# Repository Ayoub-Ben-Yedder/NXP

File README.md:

# NXP Line Following Robot

An autonomous 2line-following robot built on the Teensy microcontroller with advanced vision-based steering using Pixy2 camera. Designed for precision line tracking with intersection detection and obstacle avoidance.

## Project Overview

This project implements a sophisticated autonomous robot controller that:
- Follows lines detected by Pixy2 camera vision system
- Intelligently handles intersections and corners
- Detects and responds to obstacles using ultrasonic distance sensor
- Recognizes finish line patterns and stops safely
- Applies advanced steering algorithms for smooth, stable tracking

## Hardware Components

### Microcontroller
- **Teensy** (primary controller)

### Sensors
- **Pixy2 Camera** - Line detection and vector tracking
- **HC-SR04 Ultrasonic Sensor** - Distance measurement for obstacle detection
  - TRIG: Pin 14
  - ECHO: Pin 15

### Actuators
- **Servo Motor** - Steering control (Pin 23)
- **DC Motors (x2)** - Left and right propulsion
  - Left Motor: PWM (Pin 8), Direction (Pins 6-7)
  - Right Motor: PWM (Pin 18), Direction (Pins 20-19)

### Additional
- **LED Indicator** - Pin 22
- **Logic Level Converters** - For Pixy2 communication

## Electronics & PCB Design

The electronics are primarily a **Teensy 4.0 shield** custom designed with **KiCAD**. The shield integrates all necessary components (motor drivers, sensor interfaces, power distribution) onto a single PCB that stacks directly onto the Teensy 4.0 microcontroller, providing a clean and compact solution for the robot.

### Schematics

### PCB Layout

### 3D View

All design files are located in the `electronics/` directory.

## Mechanical Design

The mechanical design for this robot was adapted from the [NXP CUP FINALS](https://github.com/aminebensaid66/NXP-CUP-FINALS) repository. This includes the chassis, motor mounts, sensor brackets, and other structural components required for the robot assembly.

## Pin Configuration

```
PWM1 = 8      (Left motor speed)
IN1 = 6       (Left motor direction)
IN2 = 7       (Left motor direction)
PWM2 = 18     (Right motor speed)
IN3 = 20      (Right motor direction)
IN4 = 19      (Right motor direction)

LED = 22
ECHO = 15     (Ultrasonic echo)
TRIG = 14     (Ultrasonic trigger)
SERVO_PIN = 23 (Steering servo)
```

## Key Features

### 1. Advanced Line Following
- Processes up to 20 line vectors from Pixy2 camera
- Weighted steering algorithm that considers vector angles and lengths
- Minimum vector length filtering to ignore noise
- Soft steering limits to prevent oscillation

### 2. Intersection Detection
- Identifies corner types: top-left, top-right, bottom-left, bottom-right
- Analyzes angle between consecutive vectors (target ~90°)
- Applies directional corrections based on intersection position
- More aggressive steering during turns for accuracy

### 3. Steering Control
- **Center Angle:** 135° (neutral position)
- **Steering Range:** 90° (MAX_LEFT) to 180° (MAX_RIGHT)
- **Deadband:** ±15° around forward angle to filter horizontal noise
- **Soft Limiting:** Reduces extreme steering angles to prevent oscillation
- **Center Bias:** Gently pulls steering toward center for stability
- **Delay System:** Smooths steering inputs over 2 cycles

### 4. Obstacle Detection & Avoidance
- Continuously monitors distance via ultrasonic sensor
- Filtered readings (average of 3 samples) for stability
- **Stop Distance:** 15 cm - triggers reverse and stop
- Timeout handling for cases where no object is detected

### 5. Finish Line Recognition
- Detects horizontal line patterns (angle ≤ 15° from horizontal)
- Requires 2+ horizontal vectors within 5 pixels of each other
- Activation delay (10 seconds) to avoid false positives at start
- Triggers acceleration boost and obstacle check

## Build & Upload

This project uses **PlatformIO** for build and upload management.

### Prerequisites
- VSCode with PlatformIO extension
- Arduino IDE libraries (Pixy2, Servo)

### Building
```bash
pio run
```

### Uploading to Device
```bash
pio run --target upload
```

### Monitoring Serial Output
```bash
pio device monitor
```

## Algorithm Flow

1. **Initialization**
   - Configure PWM frequencies (20 kHz)
   - Initialize pins and servo to center
   - Initialize Pixy2 in line-tracking mode
   - Record start time for finish line delay

2. **Main Loop (runNXP)**
   - Read Pixy2 vectors
   - Filter vectors by length, angle, and position
   - Identify horizontal vectors for finish line detection
   - Sort vectors by length (longest first)
   - Compute steering angle based on vector count:
     - **0 vectors:** Maintain last angle
     - **1 vector:** Standard line following
     - **2+ vectors:** Check for intersection; if ~90° angle detected, apply intersection steering
   - Apply steering corrections (center bias, soft limits)
   - Implement steering delay system for smooth transitions
   - Check finish line and obstacle avoidance conditions

3. **Distance Monitoring**
   - Triggered after finish line detection
   - Backs up and stops if obstacle within STOP_DISTANCE

## Constants & Tuning Parameters

```cpp
MAX_VECTORS = 20          // Max vectors to process per frame
MIN_VECTOR_LENGTH = 10    // Minimum pixels for valid vector

CENTRE_ANGLE = 135        // Neutral steering position
MAX_RIGHT = 180           // Maximum right turn
MAX_LEFT = 90             // Maximum left turn

STOP_DISTANCE = 15        // cm - obstacle stop threshold

PIXY_FORWARD_ANGLE = 270  // Expected angle for straight tracking
PIXY_STEER_DEADBAND = 15  // Angle tolerance for horizontal detection
STEERING_DELAY_CYCLES = 2 // Smoothing delay for steering changes
STEERING_QUEUE_THRESHOLD = 2.0   // Threshold to queue steering change
STEERING_CENTER_BIAS = 5.0       // Pull toward center amount
STEERING_SOFT_LIMIT_START = 11   // When to start softening
STEERING_SOFT_LIMIT_FACTOR = 0.5 // Softening strength
CROSS_CORRECTION_ANGLE = 15      // Intersection correction
```

## Performance Notes

- **Steering Response:** Balanced between responsiveness and stability
- **Motor Speed:** Default 150 units for forward motion, 130 for finish line
- **Reverse Speed:** 100 units for obstacle avoidance
- **Frame Rate:** Dependent on Pixy2 refresh rate (typical ~50 FPS)

## Troubleshooting

| Issue | Solution |
|-------|----------|
| Robot doesn't follow line | Check Pixy2 is in "line" mode; verify camera focus; check lighting |
| Erratic steering | Increase STEERING_DELAY_CYCLES; adjust STEERING_CENTER_BIAS |
| Misses turns | Lower angle threshold in intersection detection; increase CROSS_CORRECTION_ANGLE |
| Oscillates | Enable soft limiting; increase STEERING_SOFT_LIMIT_FACTOR |
| Overshoots finish line | Reduce finish line acceleration value; increase STOP_DISTANCE |

## Project Structure

```
NXP/
├── src/
│   ├── main.cpp          # Main robot controller
│   └── README.md         # This file
├── include/
├── lib/
├── platformio.ini        # Build configuration
└── test/
```

## Future Enhancements

- PID control for smoother steering response
- Dynamic speed adjustment based on turn sharpness
- Gyro integration for improved angle estimation
- Adaptive threshold tuning based on lighting conditions
- Multi-point finish line detection for reliability

---

**Last Updated:** June 2026  
**Board:** Teensy  
**Camera:** Pixy2  
**Competition:** NXP

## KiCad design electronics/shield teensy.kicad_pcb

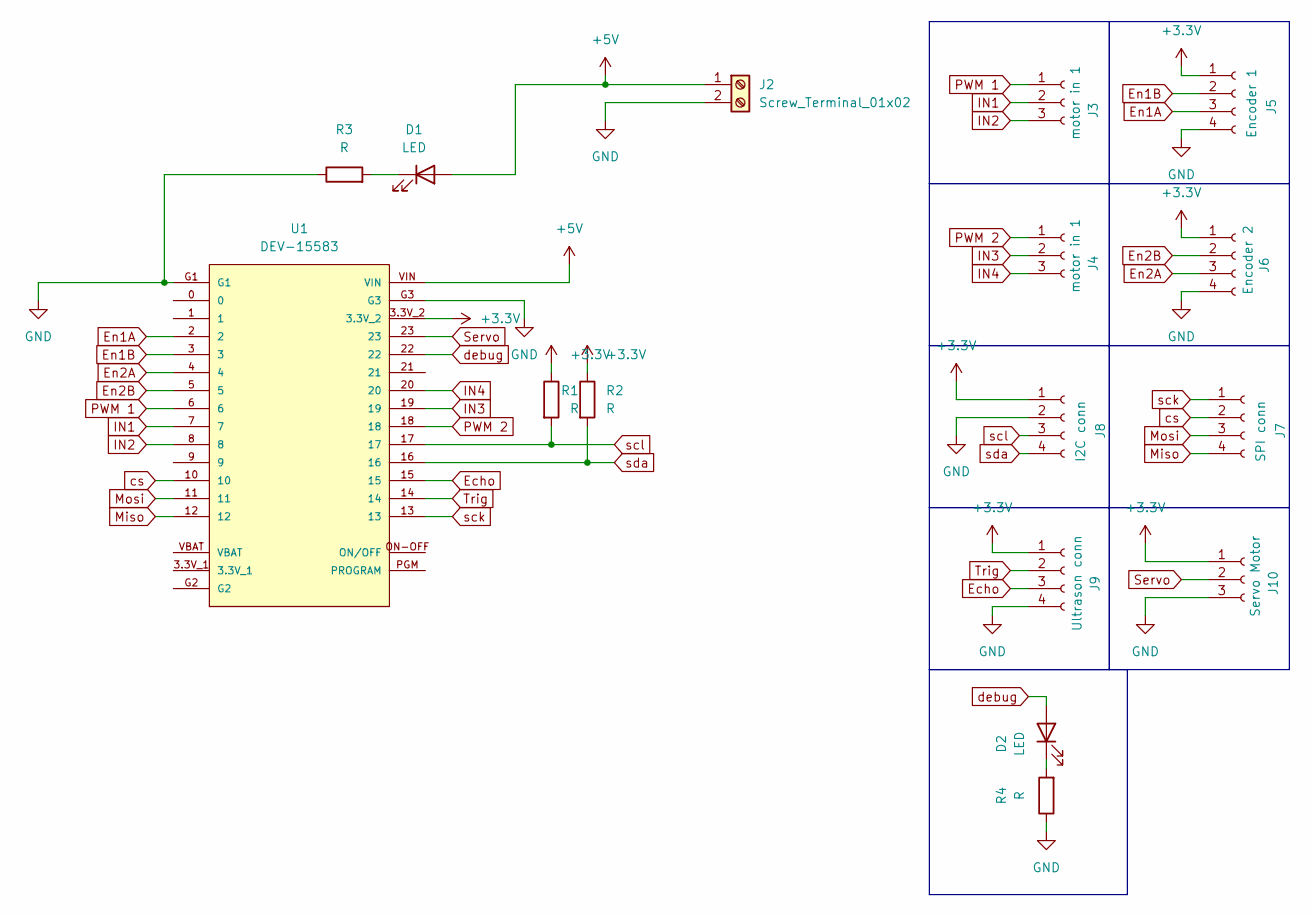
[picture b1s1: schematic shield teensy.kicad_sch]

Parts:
D1, D2: LED; LED_D3.0mm
J2: Screw_Terminal_01x02; TerminalBlock_MetzConnect_Type055_RT01502HDWU_1x02_P5.00mm_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
J3, J4: motor in 1; JST_XH_B3B-XH-A_1x03_P2.50mm_Vertical
J5: Encoder 1; JST_XH_B4B-XH-A_1x04_P2.50mm_Vertical
J6: Encoder 2; JST_XH_B4B-XH-A_1x04_P2.50mm_Vertical
J7: SPI conn; JST_XH_B4B-XH-A_1x04_P2.50mm_Vertical
J8: I2C conn; JST_XH_B4B-XH-A_1x04_P2.50mm_Vertical
J9: Ultrason conn; JST_XH_B4B-XH-A_1x04_P2.50mm_Vertical
J10: Servo Motor; JST_XH_B3B-XH-A_1x03_P2.50mm_Vertical
R1, R2: R; R_Axial_DIN0207_L6.3mm_D2.5mm_P7.62mm_Horizontal
R3, R4: R; R_Axial_DIN0207_L6.3mm_D2.5mm_P2.54mm_Vertical
U1: DEV-15583; MODULE_DEV-15583

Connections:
+3.3V: J5.1, J6.1, J8.1, J9.1, J10.1, R1.1, R2.1, U1.3.3V_2
+5V: D1.2 (A), J2.1, U1.VIN
Echo: J9.3, U1.15
En1A: J5.3, U1.2
En1B: J5.2, U1.3
En2A: J6.3, U1.4
En2B: J6.2, U1.5
GND: J2.2, J5.4, J6.4, J8.2, J9.4, J10.3, R3.1, R4.1, U1.G1, U1.G3
IN1: J3.2, U1.7
IN2: J3.3, U1.8
IN3: J4.2, U1.19
IN4: J4.3, U1.20
Miso: J7.4, U1.12
Mosi: J7.3, U1.11
unnamed: D1.1 (K), R3.2
unnamed: D2.1 (K), R4.2
PWM 1: J3.1, U1.6
PWM 2: J4.1, U1.18
Servo: J10.2, U1.23
Trig: J9.2, U1.14
cs: J7.2, U1.10
debug: D2.2 (A), U1.22
sck: J7.1, U1.13
scl: J8.3, R1.2, U1.17
sda: J8.4, R2.2, U1.16

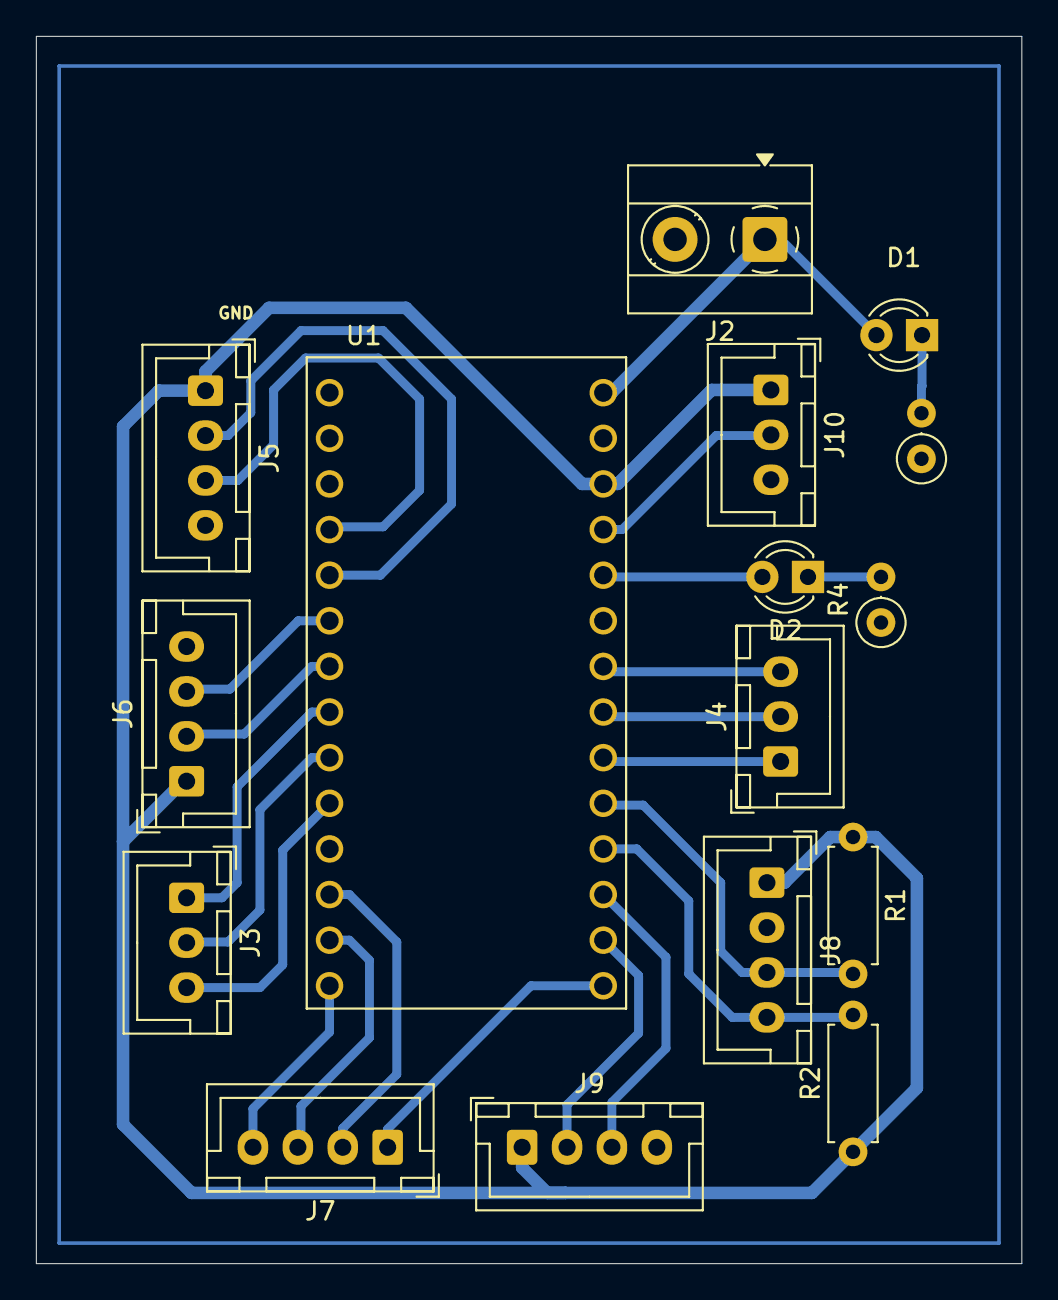
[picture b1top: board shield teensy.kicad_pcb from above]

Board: 2 copper layers, 54.9 x 68.3 mm, 16 parts (0 on the bottom side), 25 nets.

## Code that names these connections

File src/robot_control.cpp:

#include <Arduino.h>
#include <Pixy2.h>
#include <Servo.h>

#include "robot_control.h"

namespace {

constexpr uint8_t ENC_LEFT_A = 4;
constexpr uint8_t ENC_LEFT_B = 5;
constexpr uint8_t ENC_RIGHT_A = 3;
constexpr uint8_t ENC_RIGHT_B = 2;

constexpr uint8_t PWM1 = 8;
constexpr uint8_t IN1 = 6;
constexpr uint8_t IN2 = 7;
constexpr uint8_t PWM2 = 18;
constexpr uint8_t IN3 = 20;
constexpr uint8_t IN4 = 19;

constexpr uint8_t LED = 22;

constexpr uint8_t ECHO = 15;
constexpr uint8_t TRIG = 14;

constexpr uint8_t SERVO_PIN = 23;

Servo steer_servo;
Pixy2 pixy;

void leftEncoderISR() {
  if (digitalReadFast(ENC_LEFT_B) == digitalReadFast(ENC_LEFT_A)) {
    leftCount++;
  } else {
    leftCount--;
  }
}

void rightEncoderISR() {
  if (digitalReadFast(ENC_RIGHT_B) == digitalReadFast(ENC_RIGHT_A)) {
    rightCount++;
  } else {
    rightCount--;
  }
}

}  // namespace

volatile long leftCount = 0;
volatile long rightCount = 0;

void initPixy() {
  pixy.init();
  pixy.changeProg("line");
}

void steer(int angle) {
  angle = constrain(angle, MAX_LEFT, MAX_RIGHT);
  steer_servo.write(angle);
}

void run(int speedLeft, int speedRight) {
  speedLeft = constrain(speedLeft, -255, 255);
  speedRight = constrain(speedRight, -255, 255);

  if (speedRight >= 0) {
    analogWrite(PWM2, speedRight);
    digitalWrite(IN3, HIGH);
    digitalWrite(IN4, LOW);
  } else {
    analogWrite(PWM2, -speedRight);
    digitalWrite(IN3, LOW);
    digitalWrite(IN4, HIGH);
  }

  if (speedLeft >= 0) {
    analogWrite(PWM1, speedLeft);
    digitalWrite(IN1, LOW);
    digitalWrite(IN2, HIGH);
  } else {
    analogWrite(PWM1, -speedLeft);
    digitalWrite(IN1, HIGH);
    digitalWrite(IN2, LOW);
  }
}

void robot_control_setup() {
  analogWriteResolution(8);
  analogWriteFrequency(PWM1, 20000);
  analogWriteFrequency(PWM2, 20000);

  pinMode(TRIG, OUTPUT);
  pinMode(ECHO, INPUT);
  pinMode(LED, OUTPUT);

  pinMode(PWM1, OUTPUT);
  pinMode(PWM2, OUTPUT);

  pinMode(IN1, OUTPUT);
  pinMode(IN2, OUTPUT);
  pinMode(IN3, OUTPUT);
  pinMode(IN4, OUTPUT);

  pinMode(ENC_LEFT_A, INPUT_PULLUP);
  pinMode(ENC_LEFT_B, INPUT_PULLUP);
  pinMode(ENC_RIGHT_A, INPUT_PULLUP);
  pinMode(ENC_RIGHT_B, INPUT_PULLUP);

  attachInterrupt(digitalPinToInterrupt(ENC_LEFT_A), leftEncoderISR, CHANGE);
  attachInterrupt(digitalPinToInterrupt(ENC_RIGHT_A), rightEncoderISR, CHANGE);

  steer_servo.attach(SERVO_PIN);
  steer(CENTRE_ANGLE);

  initPixy();

  digitalWrite(LED, HIGH);
  run(0, 0);
}

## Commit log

2026-02-12 changed the font and the size of the vec canvas
2026-02-13 moved dashboard to another repo
2026-02-19 updated the protocole
2026-03-27 just started fr fr
2026-04-01 awel marra robot yet7arrek
2026-04-02 communication working
2026-04-02 wlh mani 3aref
2026-04-02 WE ARE HERE
2026-04-02 working but need some tuning
2026-04-02 cava a7sen chwaya
2026-04-07 version firas working better
2026-04-07 version firas
2026-04-07 version firas refactored (cleaned)
2026-04-07 Version Ayoub a7la wa7da
2026-04-07 found max x and y
2026-04-07 stopbox cava
2026-04-07 stopbox integrated
2026-04-07 added finishline detectetion only after passing it the first time
2026-04-08 tandhifa lel code
2026-04-08 teensy40 t7arget badelnaha b teensy41
2026-04-08 final inchallah marbou7a
2026-06-05 adding comments
2026-06-05 Electronics
2026-06-05 mechanical design
2026-06-05 README
